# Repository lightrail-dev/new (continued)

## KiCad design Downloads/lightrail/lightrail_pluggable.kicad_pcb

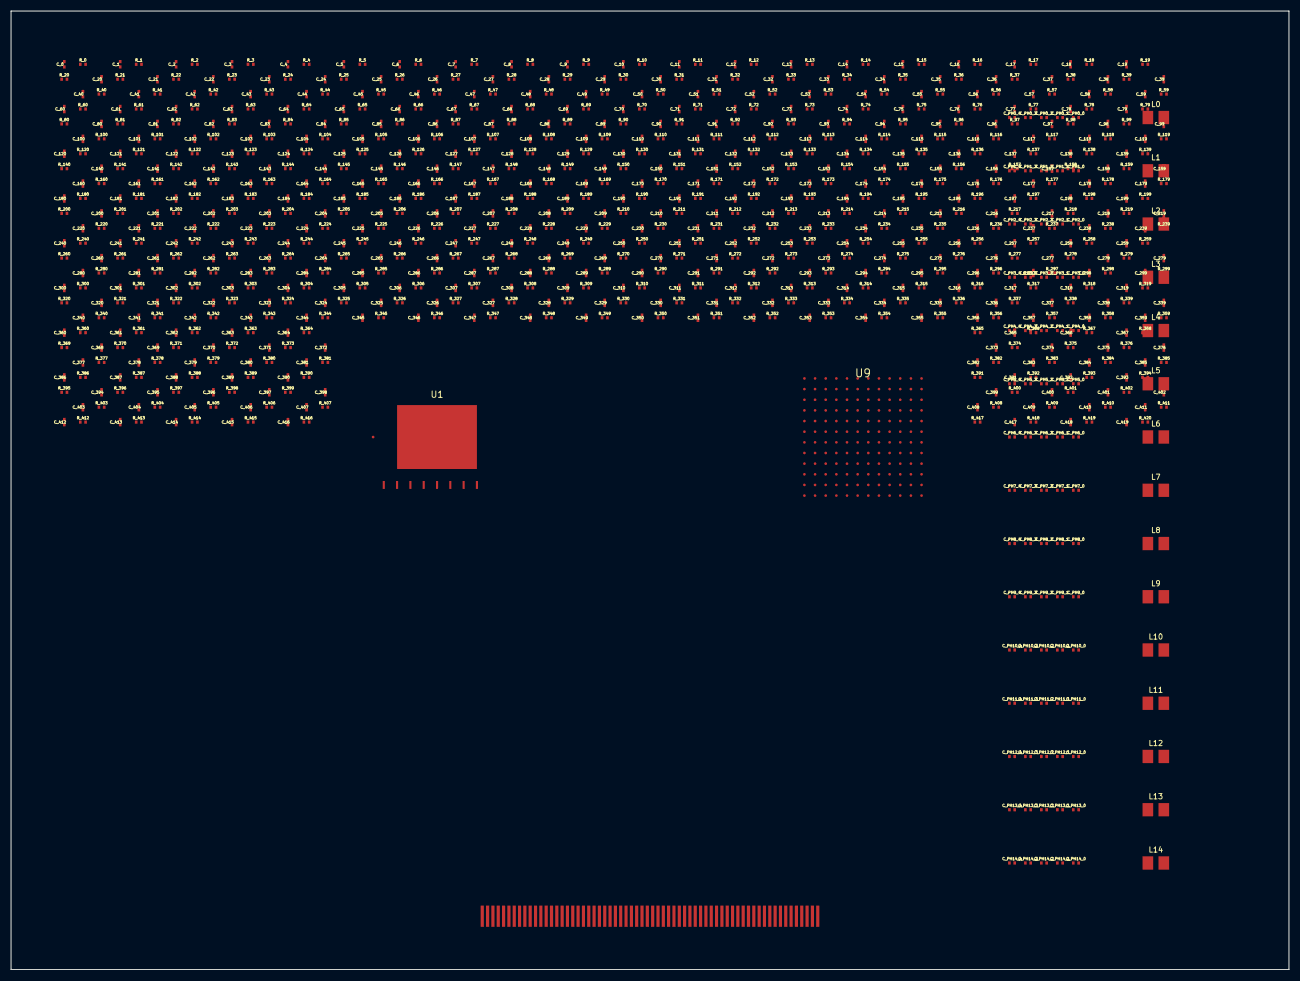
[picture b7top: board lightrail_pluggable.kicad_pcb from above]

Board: 15 copper layers, 240.0 x 180.0 mm, 933 parts (0 on the bottom side), 110 nets, no tracks yet.

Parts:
C_0, C_1, C_2, C_3, C_4, C_5, C_6, C_7, C_8, C_9, C_10, C_11, C_12, C_13, C_14, C_15, C_16, C_17, C_18, C_19, C_20, C_21, C_22, C_23, C_24, C_25, C_26, C_27, C_28, C_29, C_30, C_31, C_32, C_33, C_34, C_35, C_36, C_37, C_38, C_39, C_40, C_41, C_42, C_43, C_44, C_45, C_46, C_47, C_48, C_49, C_50, C_51, C_52, C_53, C_54, C_55, C_56, C_57, C_58, C_59, C_60, C_61, C_62, C_63, C_64, C_65, C_66, C_67, C_68, C_69, C_70, C_71, C_72, C_73, C_74, C_75, C_76, C_77, C_78, C_79, C_80, C_81, C_82, C_83, C_84, C_85, C_86, C_87, C_88, C_89, C_90, C_91, C_92, C_93, C_94, C_95, C_96, C_97, C_98, C_99, C_100, C_101, C_102, C_103, C_104, C_105, C_106, C_107, C_108, C_109, C_110, C_111, C_112, C_113, C_114, C_115, C_116, C_117, C_118, C_119, C_120, C_121, C_122, C_123, C_124, C_125, C_126, C_127, C_128, C_129, C_130, C_131, C_132, C_133, C_134, C_135, C_136, C_137, C_138, C_139, C_140, C_141, C_142, C_143, C_144, C_145, C_146, C_147, C_148, C_149, C_150, C_151, C_152, C_153, C_154, C_155, C_156, C_157, C_158, C_159, C_160, C_161, C_162, C_163, C_164, C_165, C_166, C_167, C_168, C_169, C_170, C_171, C_172, C_173, C_174, C_175, C_176, C_177, C_178, C_179, C_180, C_181, C_182, C_183, C_184, C_185, C_186, C_187, C_188, C_189, C_190, C_191, C_192, C_193, C_194, C_195, C_196, C_197, C_198, C_199, C_200, C_201, C_202, C_203, C_204, C_205, C_206, C_207, C_208, C_209, C_210, C_211, C_212, C_213, C_214, C_215, C_216, C_217, C_218, C_219, C_220, C_221, C_222, C_223, C_224, C_225, C_226, C_227, C_228, C_229, C_230, C_231, C_232, C_233, C_234, C_235, C_236, C_237, C_238, C_239, C_240, C_241, C_242, C_243, C_244, C_245, C_246, C_247, C_248, C_249, C_250, C_251, C_252, C_253, C_254, C_255, C_256, C_257, C_258, C_259, C_260, C_261, C_262, C_263, C_264, C_265, C_266, C_267, C_268, C_269, C_270, C_271, C_272, C_273, C_274, C_275, C_276, C_277, C_278, C_279, C_280, C_281, C_282, C_283, C_284, C_285, C_286, C_287, C_288, C_289, C_290, C_291, C_292, C_293, C_294, C_295, C_296, C_297, C_298, C_299, C_300, C_301, C_302, C_303, C_304, C_305, C_306, C_307, C_308, C_309, C_310, C_311, C_312, C_313, C_314, C_315, C_316, C_317, C_318, C_319, C_320, C_321, C_322, C_323, C_324, C_325, C_326, C_327, C_328, C_329, C_330, C_331, C_332, C_333, C_334, C_335, C_336, C_337, C_338, C_339, C_340, C_341, C_342, C_343, C_344, C_345, C_346, C_347, C_348, C_349, C_350, C_351, C_352, C_353, C_354, C_355, C_356, C_357, C_358, C_359, C_360, C_361, C_362, C_363, C_364, C_365, C_366, C_367, C_368, C_369, C_370, C_371, C_372, C_373, C_374, C_375, C_376, C_377, C_378, C_379, C_380, C_381, C_382, C_383, C_384, C_385, C_386, C_387, C_388, C_389, C_390, C_391, C_392, C_393, C_394, C_395, C_396, C_397, C_398, C_399, C_400, C_401, C_402, C_403, C_404, C_405, C_406, C_407, C_408, C_409, C_410, C_411, C_412, C_413, C_414, C_415, C_416, C_417, C_418, C_419: C_0402
C_PH0_0, C_PH0_1, C_PH0_2, C_PH0_3, C_PH0_4, C_PH1_0, C_PH1_1, C_PH1_2, C_PH1_3, C_PH1_4, C_PH2_0, C_PH2_1, C_PH2_2, C_PH2_3, C_PH2_4, C_PH3_0, C_PH3_1, C_PH3_2, C_PH3_3, C_PH3_4, C_PH4_0, C_PH4_1, C_PH4_2, C_PH4_3, C_PH4_4, C_PH5_0, C_PH5_1, C_PH5_2, C_PH5_3, C_PH5_4, C_PH6_0, C_PH6_1, C_PH6_2, C_PH6_3, C_PH6_4, C_PH7_0, C_PH7_1, C_PH7_2, C_PH7_3, C_PH7_4, C_PH8_0, C_PH8_1, C_PH8_2, C_PH8_3, C_PH8_4, C_PH9_0, C_PH9_1, C_PH9_2, C_PH9_3, C_PH9_4, C_PH10_0, C_PH10_1, C_PH10_2, C_PH10_3, C_PH10_4, C_PH11_0, C_PH11_1, C_PH11_2, C_PH11_3, C_PH11_4, C_PH12_0, C_PH12_1, C_PH12_2, C_PH12_3, C_PH12_4, C_PH13_0, C_PH13_1, C_PH13_2, C_PH13_3, C_PH13_4, C_PH14_0, C_PH14_1, C_PH14_2, C_PH14_3, C_PH14_4: C_0402
L0, L1, L2, L3, L4, L5, L6, L7, L8, L9, L10, L11, L12, L13, L14: L_1210
R_0, R_1, R_2, R_3, R_4, R_5, R_6, R_7, R_8, R_9, R_10, R_11, R_12, R_13, R_14, R_15, R_16, R_17, R_18, R_19, R_20, R_21, R_22, R_23, R_24, R_25, R_26, R_27, R_28, R_29, R_30, R_31, R_32, R_33, R_34, R_35, R_36, R_37, R_38, R_39, R_40, R_41, R_42, R_43, R_44, R_45, R_46, R_47, R_48, R_49, R_50, R_51, R_52, R_53, R_54, R_55, R_56, R_57, R_58, R_59, R_60, R_61, R_62, R_63, R_64, R_65, R_66, R_67, R_68, R_69, R_70, R_71, R_72, R_73, R_74, R_75, R_76, R_77, R_78, R_79, R_80, R_81, R_82, R_83, R_84, R_85, R_86, R_87, R_88, R_89, R_90, R_91, R_92, R_93, R_94, R_95, R_96, R_97, R_98, R_99, R_100, R_101, R_102, R_103, R_104, R_105, R_106, R_107, R_108, R_109, R_110, R_111, R_112, R_113, R_114, R_115, R_116, R_117, R_118, R_119, R_120, R_121, R_122, R_123, R_124, R_125, R_126, R_127, R_128, R_129, R_130, R_131, R_132, R_133, R_134, R_135, R_136, R_137, R_138, R_139, R_140, R_141, R_142, R_143, R_144, R_145, R_146, R_147, R_148, R_149, R_150, R_151, R_152, R_153, R_154, R_155, R_156, R_157, R_158, R_159, R_160, R_161, R_162, R_163, R_164, R_165, R_166, R_167, R_168, R_169, R_170, R_171, R_172, R_173, R_174, R_175, R_176, R_177, R_178, R_179, R_180, R_181, R_182, R_183, R_184, R_185, R_186, R_187, R_188, R_189, R_190, R_191, R_192, R_193, R_194, R_195, R_196, R_197, R_198, R_199, R_200, R_201, R_202, R_203, R_204, R_205, R_206, R_207, R_208, R_209, R_210, R_211, R_212, R_213, R_214, R_215, R_216, R_217, R_218, R_219, R_220, R_221, R_222, R_223, R_224, R_225, R_226, R_227, R_228, R_229, R_230, R_231, R_232, R_233, R_234, R_235, R_236, R_237, R_238, R_239, R_240, R_241, R_242, R_243, R_244, R_245, R_246, R_247, R_248, R_249, R_250, R_251, R_252, R_253, R_254, R_255, R_256, R_257, R_258, R_259, R_260, R_261, R_262, R_263, R_264, R_265, R_266, R_267, R_268, R_269, R_270, R_271, R_272, R_273, R_274, R_275, R_276, R_277, R_278, R_279, R_280, R_281, R_282, R_283, R_284, R_285, R_286, R_287, R_288, R_289, R_290, R_291, R_292, R_293, R_294, R_295, R_296, R_297, R_298, R_299, R_300, R_301, R_302, R_303, R_304, R_305, R_306, R_307, R_308, R_309, R_310, R_311, R_312, R_313, R_314, R_315, R_316, R_317, R_318, R_319, R_320, R_321, R_322, R_323, R_324, R_325, R_326, R_327, R_328, R_329, R_330, R_331, R_332, R_333, R_334, R_335, R_336, R_337, R_338, R_339, R_340, R_341, R_342, R_343, R_344, R_345, R_346, R_347, R_348, R_349, R_350, R_351, R_352, R_353, R_354, R_355, R_356, R_357, R_358, R_359, R_360, R_361, R_362, R_363, R_364, R_365, R_366, R_367, R_368, R_369, R_370, R_371, R_372, R_373, R_374, R_375, R_376, R_377, R_378, R_379, R_380, R_381, R_382, R_383, R_384, R_385, R_386, R_387, R_388, R_389, R_390, R_391, R_392, R_393, R_394, R_395, R_396, R_397, R_398, R_399, R_400, R_401, R_402, R_403, R_404, R_405, R_406, R_407, R_408, R_409, R_410, R_411, R_412, R_413, R_414, R_415, R_416, R_417, R_418, R_419, R_420: R_0402
U1: TFLN_MZM_400G
U9: BCM84881_BGA

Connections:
GND: C_0.2, C_1.2, C_2.2, C_3.2, C_4.2, C_5.2, C_6.2, C_7.2, C_8.2, C_9.2, C_10.2, C_11.2, C_12.2, C_13.2, C_14.2, C_15.2, C_16.2, C_17.2, C_18.2, C_19.2, C_20.2, C_21.2, C_22.2, C_23.2, C_24.2, C_25.2, C_26.2, C_27.2, C_28.2, C_29.2, C_30.2, C_31.2, C_32.2, C_33.2, C_34.2, C_35.2, C_36.2, C_37.2, C_38.2, C_39.2, C_40.2, C_41.2, C_42.2, C_43.2, C_44.2, C_45.2, C_46.2, C_47.2, C_48.2, C_49.2, C_50.2, C_51.2, C_52.2, C_53.2, C_54.2, C_55.2, C_56.2, C_57.2, C_58.2, C_59.2, C_60.2, C_61.2, C_62.2, C_63.2, C_64.2, C_65.2, C_66.2, C_67.2, C_68.2, C_69.2, C_70.2, C_71.2, C_72.2, C_73.2, C_74.2, C_75.2, C_76.2, C_77.2, C_78.2, C_79.2, C_80.2, C_81.2, C_82.2, C_83.2, C_84.2, C_85.2, C_86.2, C_87.2, C_88.2, C_89.2, C_90.2, C_91.2, C_92.2, C_93.2, C_94.2, C_95.2, C_96.2, C_97.2, C_98.2, C_99.2, C_100.2, C_101.2, C_102.2, C_103.2, C_104.2, C_105.2, C_106.2, C_107.2, C_108.2, C_109.2, C_110.2, C_111.2, C_112.2, C_113.2, C_114.2, C_115.2, C_116.2, C_117.2, C_118.2, C_119.2, C_120.2, C_121.2, C_122.2, C_123.2, C_124.2, C_125.2, C_126.2, C_127.2, C_128.2, C_129.2, C_130.2, C_131.2, C_132.2, C_133.2, C_134.2, C_135.2, C_136.2, C_137.2, C_138.2, C_139.2, C_140.2, C_141.2, C_142.2, C_143.2, C_144.2, C_145.2, C_146.2, C_147.2, C_148.2, C_149.2, C_150.2, C_151.2, C_152.2, C_153.2, C_154.2, C_155.2, C_156.2, C_157.2, C_158.2, C_159.2, C_160.2, C_161.2, C_162.2, C_163.2, C_164.2, C_165.2, C_166.2, C_167.2, C_168.2, C_169.2, C_170.2, C_171.2, C_172.2, C_173.2, C_174.2, C_175.2, C_176.2, C_177.2, C_178.2, C_179.2, C_180.2, C_181.2, C_182.2, C_183.2, C_184.2, C_185.2, C_186.2, C_187.2, C_188.2, C_189.2, C_190.2, C_191.2, C_192.2, C_193.2, C_194.2, C_195.2, C_196.2, C_197.2, C_198.2, C_199.2, C_200.2, C_201.2, C_202.2, C_203.2, C_204.2, C_205.2, C_206.2, C_207.2, C_208.2, C_209.2, C_210.2, C_211.2, C_212.2, C_213.2, C_214.2, C_215.2, C_216.2, C_217.2, C_218.2, C_219.2, C_220.2, C_221.2, C_222.2, C_223.2, C_224.2, C_225.2, C_226.2, C_227.2, C_228.2, C_229.2, C_230.2, C_231.2, C_232.2, C_233.2, C_234.2, C_235.2, C_236.2, C_237.2, C_238.2, C_239.2, C_240.2, C_241.2, C_242.2, C_243.2, C_244.2, C_245.2, C_246.2, C_247.2, C_248.2, C_249.2, C_250.2, C_251.2, C_252.2, C_253.2, C_254.2, C_255.2, C_256.2, C_257.2, C_258.2, C_259.2, C_260.2, C_261.2, C_262.2, C_263.2, C_264.2, C_265.2, C_266.2, C_267.2, C_268.2, C_269.2, C_270.2, C_271.2, C_272.2, C_273.2, C_274.2, C_275.2, C_276.2, C_277.2, C_278.2, C_279.2, C_280.2, C_281.2, C_282.2, C_283.2, C_284.2, C_285.2, C_286.2, C_287.2, C_288.2, C_289.2, C_290.2, C_291.2, C_292.2, C_293.2, C_294.2, C_295.2, C_296.2, C_297.2, C_298.2, C_299.2, C_300.2, C_301.2, C_302.2, C_303.2, C_304.2, C_305.2, C_306.2, C_307.2, C_308.2, C_309.2, C_310.2, C_311.2, C_312.2, C_313.2, C_314.2, C_315.2, C_316.2, C_317.2, C_318.2, C_319.2, C_320.2, C_321.2, C_322.2, C_323.2, C_324.2, C_325.2, C_326.2, C_327.2, C_328.2, C_329.2, C_330.2, C_331.2, C_332.2, C_333.2, C_334.2, C_335.2, C_336.2, C_337.2, C_338.2, C_339.2, C_340.2, C_341.2, C_342.2, C_343.2, C_344.2, C_345.2, C_346.2, C_347.2, C_348.2, C_349.2, C_350.2, C_351.2, C_352.2, C_353.2, C_354.2, C_355.2, C_356.2, C_357.2, C_358.2, C_359.2, C_360.2, C_361.2, C_362.2, C_363.2, C_364.2, C_365.2, C_366.2, C_367.2, C_368.2, C_369.2, C_370.2, C_371.2, C_372.2, C_373.2, C_374.2, C_375.2, C_376.2, C_377.2, C_378.2, C_379.2, C_380.2, C_381.2, C_382.2, C_383.2, C_384.2, C_385.2, C_386.2, C_387.2, C_388.2, C_389.2, C_390.2, C_391.2, C_392.2, C_393.2, C_394.2, C_395.2, C_396.2, C_397.2, C_398.2, C_399.2, C_400.2, C_401.2, C_402.2, C_403.2, C_404.2, C_405.2, C_406.2, C_407.2, C_408.2, C_409.2, C_410.2, C_411.2, C_412.2, C_413.2, C_414.2, C_415.2, C_416.2, C_417.2, C_418.2, C_419.2, C_PH0_0.2, C_PH0_1.2, C_PH0_2.2, C_PH0_3.2, C_PH0_4.2, C_PH1_0.2, C_PH1_1.2, C_PH1_2.2, C_PH1_3.2, C_PH1_4.2, C_PH2_0.2, C_PH2_1.2, C_PH2_2.2, C_PH2_3.2, C_PH2_4.2, C_PH3_0.2, C_PH3_1.2, C_PH3_2.2, C_PH3_3.2, C_PH3_4.2, C_PH4_0.2, C_PH4_1.2, C_PH4_2.2, C_PH4_3.2, C_PH4_4.2, C_PH5_0.2, C_PH5_1.2, C_PH5_2.2, C_PH5_3.2, C_PH5_4.2, C_PH6_0.2, C_PH6_1.2, C_PH6_2.2, C_PH6_3.2, C_PH6_4.2, C_PH7_0.2, C_PH7_1.2, C_PH7_2.2, C_PH7_3.2, C_PH7_4.2, C_PH8_0.2, C_PH8_1.2, C_PH8_2.2, C_PH8_3.2, C_PH8_4.2, C_PH9_0.2, C_PH9_1.2, C_PH9_2.2, C_PH9_3.2, C_PH9_4.2, C_PH10_0.2, C_PH10_1.2, C_PH10_2.2, C_PH10_3.2, C_PH10_4.2, C_PH11_0.2, C_PH11_1.2, C_PH11_2.2, C_PH11_3.2, C_PH11_4.2, C_PH12_0.2, C_PH12_1.2, C_PH12_2.2, C_PH12_3.2, C_PH12_4.2, C_PH13_0.2, C_PH13_1.2, C_PH13_2.2, C_PH13_3.2, C_PH13_4.2, C_PH14_0.2, C_PH14_1.2, C_PH14_2.2, C_PH14_3.2, C_PH14_4.2, R_0.2, R_1.2, R_2.2, R_3.2, R_4.2, R_5.2, R_6.2, R_7.2, R_8.2, R_9.2, R_10.2, R_11.2, R_12.2, R_13.2, R_14.2, R_15.2, R_16.2, R_17.2, R_18.2, R_19.2, R_20.2, R_21.2, R_22.2, R_23.2, R_24.2, R_25.2, R_26.2, R_27.2, R_28.2, R_29.2, R_30.2, R_31.2, R_32.2, R_33.2, R_34.2, R_35.2, R_36.2, R_37.2, R_38.2, R_39.2, R_40.2, R_41.2, R_42.2, R_43.2, R_44.2, R_45.2, R_46.2, R_47.2, R_48.2, R_49.2, R_50.2, R_51.2, R_52.2, R_53.2, R_54.2, R_55.2, R_56.2, R_57.2, R_58.2, R_59.2, R_60.2, R_61.2, R_62.2, R_63.2, R_64.2, R_65.2, R_66.2, R_67.2, R_68.2, R_69.2, R_70.2, R_71.2, R_72.2, R_73.2, R_74.2, R_75.2, R_76.2, R_77.2, R_78.2, R_79.2, R_80.2, R_81.2, R_82.2, R_83.2, R_84.2, R_85.2, R_86.2, R_87.2, R_88.2, R_89.2, R_90.2, R_91.2, R_92.2, R_93.2, R_94.2, R_95.2, R_96.2, R_97.2, R_98.2, R_99.2, R_100.2, R_101.2, R_102.2, R_103.2, R_104.2, R_105.2, R_106.2, R_107.2, R_108.2, R_109.2, R_110.2, R_111.2, R_112.2, R_113.2, R_114.2, R_115.2, R_116.2, R_117.2, R_118.2, R_119.2, R_120.2, R_121.2, R_122.2, R_123.2, R_124.2, R_125.2, R_126.2, R_127.2, R_128.2, R_129.2, R_130.2, R_131.2, R_132.2, R_133.2, R_134.2, R_135.2, R_136.2, R_137.2, R_138.2, R_139.2, R_140.2, R_141.2, R_142.2, R_143.2, R_144.2, R_145.2, R_146.2, R_147.2, R_148.2, R_149.2, R_150.2, R_151.2, R_152.2, R_153.2, R_154.2, R_155.2, R_156.2, R_157.2, R_158.2, R_159.2, R_160.2, R_161.2, R_162.2, R_163.2, R_164.2, R_165.2, R_166.2, R_167.2, R_168.2, R_169.2, R_170.2, R_171.2, R_172.2, R_173.2, R_174.2, R_175.2, R_176.2, R_177.2, R_178.2, R_179.2, R_180.2, R_181.2, R_182.2, R_183.2, R_184.2, R_185.2, R_186.2, R_187.2, R_188.2, R_189.2, R_190.2, R_191.2, R_192.2, R_193.2, R_194.2, R_195.2, R_196.2, R_197.2, R_198.2, R_199.2, R_200.2, R_201.2, R_202.2, R_203.2, R_204.2, R_205.2, R_206.2, R_207.2, R_208.2, R_209.2, R_210.2, R_211.2, R_212.2, R_213.2, R_214.2, R_215.2, R_216.2, R_217.2, R_218.2, R_219.2, R_220.2, R_221.2, R_222.2, R_223.2, R_224.2, R_225.2, R_226.2, R_227.2, R_228.2, R_229.2, R_230.2, R_231.2, R_232.2, R_233.2, R_234.2, R_235.2, R_236.2, R_237.2, R_238.2, R_239.2, R_240.2, R_241.2, R_242.2, R_243.2, R_244.2, R_245.2, R_246.2, R_247.2, R_248.2, R_249.2, R_250.2, R_251.2, R_252.2, R_253.2, R_254.2, R_255.2, R_256.2, R_257.2, R_258.2, R_259.2, R_260.2, R_261.2, R_262.2, R_263.2, R_264.2, R_265.2, R_266.2, R_267.2, R_268.2, R_269.2, R_270.2, R_271.2, R_272.2, R_273.2, R_274.2, R_275.2, R_276.2, R_277.2, R_278.2, R_279.2, R_280.2, R_281.2, R_282.2, R_283.2, R_284.2, R_285.2, R_286.2, R_287.2, R_288.2, R_289.2, R_290.2, R_291.2, R_292.2, R_293.2, R_294.2, R_295.2, R_296.2, R_297.2, R_298.2, R_299.2, R_300.2, R_301.2, R_302.2, R_303.2, R_304.2, R_305.2, R_306.2, R_307.2, R_308.2, R_309.2, R_310.2, R_311.2, R_312.2, R_313.2, R_314.2, R_315.2, R_316.2, R_317.2, R_318.2, R_319.2, R_320.2, R_321.2, R_322.2, R_323.2, R_324.2, R_325.2, R_326.2, R_327.2, R_328.2, R_329.2, R_330.2, R_331.2, R_332.2, R_333.2, R_334.2, R_335.2, R_336.2, R_337.2, R_338.2, R_339.2, R_340.2, R_341.2, R_342.2, R_343.2, R_344.2, R_345.2, R_346.2, R_347.2, R_348.2, R_349.2, R_350.2, R_351.2, R_352.2, R_353.2, R_354.2, R_355.2, R_356.2, R_357.2, R_358.2, R_359.2, R_360.2, R_361.2, R_362.2, R_363.2, R_364.2, R_365.2, R_366.2, R_367.2, R_368.2, R_369.2, R_370.2, R_371.2, R_372.2, R_373.2, R_374.2, R_375.2, R_376.2, R_377.2, R_378.2, R_379.2, R_380.2, R_381.2, R_382.2, R_383.2, R_384.2, R_385.2, R_386.2, R_387.2, R_388.2, R_389.2, R_390.2, R_391.2, R_392.2, R_393.2, R_394.2, R_395.2, R_396.2, R_397.2, R_398.2, R_399.2, R_400.2, R_401.2, R_402.2, R_403.2, R_404.2, R_405.2, R_406.2, R_407.2, R_408.2, R_409.2, R_410.2, R_411.2, R_412.2, R_413.2, R_414.2, R_415.2, R_416.2, R_417.2, R_418.2, R_419.2, R_420.2, U1.TH
SIG_0: R_34.1, R_60.1, R_75.1, R_123.1, R_291.1, R_345.1, U9.8_4
SIG_1: R_28.1, R_126.1, R_140.1, R_387.1, U9.8_5
SIG_2: R_93.1, R_114.1, R_294.1, U9.8_6
SIG_3: R_76.1, R_82.1, R_175.1, R_228.1, U9.8_7
SIG_4: R_68.1, R_196.1, R_200.1, R_213.1, R_250.1, R_251.1, R_290.1, R_358.1, U9.8_8
SIG_5: R_109.1, R_416.1, R_419.1, U9.8_9
SIG_6: R_212.1, R_261.1, R_335.1, R_351.1, R_384.1, R_394.1, U9.8_10
SIG_7: R_31.1, R_49.1, R_73.1, R_80.1, R_113.1, U9.8_11
SIG_8: R_88.1, R_115.1, R_264.1, U9.9_0
SIG_9: R_129.1, R_282.1, R_288.1, R_317.1, U9.9_1
SIG_10: R_147.1, U9.9_2
SIG_11: R_409.1, U9.9_3
SIG_12: R_230.1, R_391.1, U9.9_4
SIG_13: R_156.1, R_202.1, R_389.1, R_404.1, U9.9_5
SIG_14: R_186.1, R_243.1, R_255.1, R_273.1, R_352.1, R_365.1, R_397.1, R_405.1, R_410.1, U9.9_6
SIG_15: R_1.1, R_25.1, R_53.1, R_74.1, R_112.1, R_143.1, R_180.1, R_309.1, R_399.1, U9.9_7
SIG_16: R_204.1, R_217.1, R_237.1, U9.9_8
SIG_17: R_218.1, R_234.1, R_266.1, R_321.1, R_401.1, U9.9_9
SIG_18: R_222.1, R_271.1, R_372.1, U9.9_10
SIG_19: R_18.1, R_55.1, R_135.1, R_305.1, R_320.1, U9.9_11
SIG_20: R_4.1, R_209.1, R_377.1
SIG_21: R_70.1, R_102.1, R_105.1, R_388.1
SIG_22: R_54.1, R_145.1, R_238.1
SIG_23: R_280.1, R_316.1
SIG_24: R_151.1, R_165.1, R_314.1
SIG_25: R_50.1, R_239.1, R_382.1
SIG_26: R_127.1, R_268.1, R_333.1
SIG_28: R_32.1, R_97.1, R_111.1, R_272.1, R_298.1
SIG_29: R_43.1, R_285.1, R_292.1, R_362.1
SIG_30: R_155.1, R_195.1, R_295.1, R_318.1
SIG_31: R_5.1, R_36.1, R_71.1, R_92.1, R_100.1, R_176.1
SIG_32: R_30.1, R_94.1, R_177.1, R_184.1, R_247.1, R_402.1
SIG_33: R_72.1, R_132.1, R_210.1, R_211.1, R_219.1, R_332.1, R_383.1
SIG_34: R_37.1, R_240.1, R_408.1
SIG_35: R_8.1, R_95.1, R_133.1, R_201.1, R_215.1, R_311.1, R_337.1, R_417.1
SIG_36: R_101.1, R_252.1
SIG_37: R_14.1, R_33.1, R_106.1, R_139.1, R_157.1, R_198.1
SIG_38: R_17.1, R_19.1, R_191.1
SIG_39: R_56.1, R_141.1, R_203.1, R_281.1, R_334.1, R_361.1, R_374.1
SIG_40: R_182.1, R_223.1, R_265.1, R_339.1
SIG_41: R_77.1, R_121.1, R_286.1, R_302.1, R_330.1
SIG_42: R_3.1, R_179.1
SIG_43: R_183.1, R_188.1, R_279.1
SIG_44: R_44.1, R_168.1, R_233.1, R_267.1, R_308.1, R_323.1, R_392.1
SIG_45: R_22.1, R_66.1, R_246.1, R_395.1
SIG_46: R_21.1, R_24.1, R_244.1, R_400.1
SIG_47: R_124.1, R_312.1, R_327.1, R_328.1, R_371.1, R_393.1
SIG_48: R_46.1, R_144.1, R_306.1, R_390.1
SIG_49: R_216.1, R_307.1
SIG_50: R_83.1, R_134.1, R_283.1, R_353.1
SIG_51: R_13.1, R_38.1
SIG_52: R_45.1, R_69.1, R_245.1, R_296.1, R_396.1
SIG_53: R_40.1, R_122.1, R_221.1, R_235.1, R_357.1
SIG_54: R_57.1, R_259.1, R_338.1
SIG_55: R_300.1, R_364.1, R_407.1
SIG_56: R_163.1, R_205.1, R_299.1, R_301.1, R_403.1
SIG_57: R_9.1, R_39.1, R_185.1, R_236.1, R_278.1, R_329.1, R_342.1, R_420.1
SIG_58: R_6.1, R_90.1, R_149.1, R_263.1, R_269.1
SIG_59: R_12.1, R_153.1, R_277.1, R_418.1
SIG_60: R_174.1, R_224.1, R_241.1, R_348.1
SIG_61: R_199.1, R_347.1, R_350.1
SIG_62: R_326.1, R_336.1, R_343.1, R_411.1
SIG_63: R_20.1, R_42.1, R_96.1, R_232.1, R_324.1
SIG_64: R_171.1, R_406.1
SIG_65: R_89.1, R_136.1, R_225.1, R_231.1, R_363.1
SIG_66: R_48.1, R_242.1, R_284.1, R_297.1, R_331.1, R_360.1, R_366.1
SIG_67: R_81.1, R_117.1, R_303.1
SIG_68: R_67.1, R_150.1, R_274.1
SIG_70: R_118.1, R_172.1, R_226.1, R_344.1, R_369.1, R_414.1
SIG_72: R_78.1, R_207.1, R_319.1, R_325.1, U9.6_0
SIG_73: R_2.1, R_128.1, R_356.1, U9.6_1
SIG_74: R_178.1, R_256.1, R_304.1, U9.6_2
SIG_75: R_52.1, R_158.1, R_315.1, R_370.1, U9.6_3
SIG_76: R_7.1, R_15.1, R_192.1, R_193.1, R_378.1, U9.6_4
SIG_77: R_11.1, R_26.1, R_86.1, R_99.1, R_368.1, R_386.1, U9.6_5
SIG_78: R_130.1, R_142.1, R_376.1, U9.6_6
SIG_79: R_65.1, R_148.1, R_253.1, R_293.1, R_359.1, U9.6_7
SIG_80: R_59.1, R_120.1, R_160.1, R_164.1, R_214.1, R_367.1, R_413.1, U9.6_8
SIG_81: R_27.1, R_61.1, R_138.1, R_220.1, R_229.1, R_257.1, U9.6_9
SIG_82: R_41.1, R_119.1, R_249.1, R_289.1, R_379.1, U9.6_10
SIG_83: R_248.1, R_260.1, U9.6_11
SIG_84: R_47.1, R_355.1, U9.7_0
SIG_85: R_51.1, R_87.1, R_137.1, R_194.1, R_270.1, U9.7_1
SIG_86: R_167.1, R_310.1, R_373.1, U9.7_2
SIG_87: R_146.1, R_162.1, R_166.1, R_197.1, R_206.1, R_275.1, R_349.1, U9.7_3
SIG_88: R_63.1, R_181.1, R_254.1, U9.7_4
SIG_89: R_116.1, R_152.1, R_161.1, R_169.1, R_258.1, R_276.1, R_287.1, U9.7_5
SIG_90: R_10.1, R_98.1, R_131.1, R_322.1, R_354.1, U9.7_6
SIG_91: R_23.1, R_103.1, R_170.1, R_227.1, U9.7_7
SIG_92: R_62.1, R_187.1, R_346.1, R_385.1, U9.7_8
SIG_93: R_35.1, R_79.1, R_398.1, R_412.1, U9.7_9
SIG_94: R_84.1, R_125.1, R_173.1, R_189.1, R_262.1, R_341.1, U9.7_10
SIG_95: R_0.1, R_104.1, R_108.1, R_110.1, R_208.1, U9.7_11
SIG_96: R_58.1, R_91.1, R_380.1, R_381.1, U9.8_0
SIG_97: R_29.1, U9.8_1
SIG_98: R_64.1, R_190.1, R_340.1, U9.8_2
SIG_99: R_16.1, R_85.1, R_154.1, R_313.1, R_415.1, U9.8_3
TFLN_RF_CH0: U1.0, U9.5_4
TFLN_RF_CH1: U1.1, U9.5_5
TFLN_RF_CH2: U1.2, U9.5_6
TFLN_RF_CH3: U1.3, U9.5_7
TFLN_RF_CH4: U1.4, U9.5_8
TFLN_RF_CH5: U1.5, U9.5_9
TFLN_RF_CH6: U1.6, U9.5_10
TFLN_RF_CH7: U1.7, U9.5_11
VCC_1V8: C_6.1, C_7.1, C_12.1, C_13.1, C_16.1, C_18.1, C_19.1, C_21.1, C_23.1, C_26.1, C_30.1, C_34.1, C_35.1, C_40.1, C_43.1, C_44.1, C_46.1, C_50.1, C_52.1, C_53.1, C_54.1, C_55.1, C_56.1, C_57.1, C_59.1, C_62.1, C_66.1, C_78.1, C_82.1, C_86.1, C_88.1, C_95.1, C_104.1, C_109.1, C_110.1, C_115.1, C_116.1, C_120.1, C_125.1, C_130.1, C_131.1, C_133.1, C_135.1, C_137.1, C_143.1, C_147.1, C_151.1, C_152.1, C_156.1, C_158.1, C_161.1, C_165.1, C_166.1, C_171.1, C_172.1, C_176.1, C_184.1, C_187.1, C_188.1, C_193.1, C_197.1, C_198.1, C_203.1, C_210.1, C_211.1, C_220.1, C_224.1, C_225.1, C_226.1, C_229.1, C_232.1, C_234.1, C_238.1, C_239.1, C_245.1, C_252.1, C_253.1, C_256.1, C_258.1, C_262.1, C_266.1, C_278.1, C_280.1, C_283.1, C_292.1, C_295.1, C_297.1, C_299.1, C_301.1, C_302.1, C_305.1, C_306.1, C_310.1, C_314.1, C_318.1, C_320.1, C_321.1, C_326.1, C_335.1, C_337.1, C_338.1, C_340.1, C_344.1, C_348.1, C_352.1, C_356.1, C_357.1, C_359.1, C_361.1, C_363.1, C_370.1, C_383.1, C_387.1, C_388.1, C_389.1, C_391.1, C_395.1, C_396.1, C_398.1, C_400.1, C_405.1, C_406.1, C_407.1, C_408.1, C_409.1, C_410.1, C_411.1, C_412.1, C_414.1, C_415.1, C_417.1, C_419.1, C_PH0_0.1, C_PH0_1.1, C_PH0_2.1, C_PH0_3.1, C_PH0_4.1, C_PH1_0.1, C_PH1_1.1, C_PH1_2.1, C_PH1_3.1, C_PH1_4.1, C_PH2_0.1, C_PH2_1.1, C_PH2_2.1, C_PH2_3.1, C_PH2_4.1, C_PH3_0.1, C_PH3_1.1, C_PH3_2.1, C_PH3_3.1, C_PH3_4.1, C_PH4_0.1, C_PH4_1.1, C_PH4_2.1, C_PH4_3.1, C_PH4_4.1, C_PH5_0.1, C_PH5_1.1, C_PH5_2.1, C_PH5_3.1, C_PH5_4.1, C_PH6_0.1, C_PH6_1.1, C_PH6_2.1, C_PH6_3.1, C_PH6_4.1, C_PH7_0.1, C_PH7_1.1, C_PH7_2.1, C_PH7_3.1, C_PH7_4.1, C_PH8_0.1, C_PH8_1.1, C_PH8_2.1, C_PH8_3.1, C_PH8_4.1, C_PH9_0.1, C_PH9_1.1, C_PH9_2.1, C_PH9_3.1, C_PH9_4.1, C_PH10_0.1, C_PH10_1.1, C_PH10_2.1, C_PH10_3.1, C_PH10_4.1, C_PH11_0.1, C_PH11_1.1, C_PH11_2.1, C_PH11_3.1, C_PH11_4.1, C_PH12_0.1, C_PH12_1.1, C_PH12_2.1, C_PH12_3.1, C_PH12_4.1, C_PH13_0.1, C_PH13_1.1, C_PH13_2.1, C_PH13_3.1, C_PH13_4.1, C_PH14_0.1, C_PH14_1.1, C_PH14_2.1, C_PH14_3.1, C_PH14_4.1, L0.2, L1.2, L2.2, L3.2, L4.2, L5.2, L6.2, L7.2, L8.2, L9.2, L10.2, L11.2, L12.2, L13.2, L14.2, U9.10_0, U9.10_1, U9.10_2, U9.10_3, U9.10_4, U9.10_5, U9.10_6, U9.10_7, U9.10_8, U9.10_9, U9.10_10, U9.10_11, U9.11_0, U9.11_1, U9.11_2, U9.11_3, U9.11_4, U9.11_5, U9.11_6, U9.11_7, U9.11_8, U9.11_9, U9.11_10, U9.11_11
VCC_3V3: C_1.1, C_8.1, C_14.1, C_15.1, C_20.1, C_27.1, C_32.1, C_37.1, C_38.1, C_41.1, C_45.1, C_47.1, C_51.1, C_67.1, C_69.1, C_70.1, C_72.1, C_73.1, C_79.1, C_84.1, C_85.1, C_87.1, C_90.1, C_91.1, C_94.1, C_99.1, C_102.1, C_103.1, C_107.1, C_108.1, C_114.1, C_117.1, C_124.1, C_127.1, C_128.1, C_132.1, C_134.1, C_136.1, C_138.1, C_141.1, C_142.1, C_146.1, C_149.1, C_150.1, C_153.1, C_154.1, C_155.1, C_157.1, C_159.1, C_164.1, C_167.1, C_170.1, C_173.1, C_177.1, C_178.1, C_183.1, C_185.1, C_190.1, C_191.1, C_194.1, C_200.1, C_204.1, C_205.1, C_206.1, C_207.1, C_208.1, C_209.1, C_212.1, C_213.1, C_214.1, C_215.1, C_216.1, C_217.1, C_218.1, C_222.1, C_227.1, C_228.1, C_230.1, C_233.1, C_236.1, C_237.1, C_240.1, C_246.1, C_250.1, C_254.1, C_255.1, C_259.1, C_261.1, C_263.1, C_264.1, C_267.1, C_268.1, C_269.1, C_272.1, C_273.1, C_274.1, C_276.1, C_279.1, C_285.1, C_287.1, C_288.1, C_291.1, C_293.1, C_296.1, C_303.1, C_304.1, C_309.1, C_311.1, C_313.1, C_316.1, C_319.1, C_322.1, C_324.1, C_325.1, C_330.1, C_332.1, C_343.1, C_346.1, C_347.1, C_350.1, C_355.1, C_362.1, C_364.1, C_365.1, C_366.1, C_367.1, C_368.1, C_369.1, C_372.1, C_373.1, C_374.1, C_378.1, C_381.1, C_384.1, C_386.1, C_390.1, C_397.1, C_416.1, C_418.1
VCC_12V: L0.1, L1.1, L2.1, L3.1, L4.1, L5.1, L6.1, L7.1, L8.1, L9.1, L10.1, L11.1, L12.1, L13.1, L14.1
V_BIAS: C_0.1, C_2.1, C_3.1, C_4.1, C_5.1, C_9.1, C_10.1, C_11.1, C_17.1, C_22.1, C_24.1, C_25.1, C_28.1, C_29.1, C_31.1, C_33.1, C_36.1, C_39.1, C_42.1, C_48.1, C_49.1, C_58.1, C_60.1, C_61.1, C_63.1, C_64.1, C_65.1, C_68.1, C_71.1, C_74.1, C_75.1, C_76.1, C_77.1, C_80.1, C_81.1, C_83.1, C_89.1, C_92.1, C_93.1, C_96.1, C_97.1, C_98.1, C_100.1, C_101.1, C_105.1, C_106.1, C_111.1, C_112.1, C_113.1, C_118.1, C_119.1, C_121.1, C_122.1, C_123.1, C_126.1, C_129.1, C_139.1, C_140.1, C_144.1, C_145.1, C_148.1, C_160.1, C_162.1, C_163.1, C_168.1, C_169.1, C_174.1, C_175.1, C_179.1, C_180.1, C_181.1, C_182.1, C_186.1, C_189.1, C_192.1, C_195.1, C_196.1, C_199.1, C_201.1, C_202.1, C_219.1, C_221.1, C_223.1, C_231.1, C_235.1, C_241.1, C_242.1, C_243.1, C_244.1, C_247.1, C_248.1, C_249.1, C_251.1, C_257.1, C_260.1, C_265.1, C_270.1, C_271.1, C_275.1, C_277.1, C_281.1, C_282.1, C_284.1, C_286.1, C_289.1, C_290.1, C_294.1, C_298.1, C_300.1, C_307.1, C_308.1, C_312.1, C_315.1, C_317.1, C_323.1, C_327.1, C_328.1, C_329.1, C_331.1, C_333.1, C_334.1, C_336.1, C_339.1, C_341.1, C_342.1, C_345.1, C_349.1, C_351.1, C_353.1, C_354.1, C_358.1, C_360.1, C_371.1, C_375.1, C_376.1, C_377.1, C_379.1, C_380.1, C_382.1, C_385.1, C_392.1, C_393.1, C_394.1, C_399.1, C_401.1, C_402.1, C_403.1, C_404.1, C_413.1

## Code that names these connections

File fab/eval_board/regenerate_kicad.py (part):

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\t\t(pin "+1V0" input (at 88.9 85.09 180) (effects (font (size 1.27 1.27))) (uuid "{uid()}"))
\t\t(pin "+1V8" input (at 88.9 87.63 180) (effects (font (size 1.27 1.27))) (uuid "{uid()}"))
\t\t(pin "+3V3" input (at 88.9 90.17 180) (effects (font (size 1.27 1.27))) (uuid "{uid()}"))
\t\t(pin "AXI_ACLK" bidirectional (at 133.35 82.55 0) (effects (font (size 1.27 1.27))) (uuid "{uid()}"))
\t\t(pin "JTAG_TDO" output (at 133.35 85.09 0) (effects (font (size 1.27 1.27))) (uuid "{uid()}"))
\t\t(pin "TFLN_TX_P" output (at 133.35 87.63 0) (effects (font (size 1.27 1.27))) (uuid "{uid()}"))
\t\t(pin "HBM_DQ" bidirectional (at 133.35 90.17 0) (effects (font (size 1.27 1.27))) (uuid "{uid()}"))
\t)""")
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\t\t(property "Sheetname" "TFLN_Optical" (at 152.4 74.93 0) (effects (font (size 1.27 1.27))))
\t\t(property "Sheetfile" "sheets/tfln_optical.kicad_sch" (at 152.4 104.14 0) (effects (font (size 1.27 1.27)) (hide yes)))
\t\t(pin "TFLN_TX_P" input (at 152.4 82.55 180) (effects (font (size 1.27 1.27))) (uuid "{uid()}"))
\t\t(pin "SPI_CLK" input (at 152.4 87.63 180) (effects (font (size 1.27 1.27))) (uuid "{uid()}"))
\t\t(pin "I2C_SCL" bidirectional (at 190.5 82.55 0) (effects (font (size 1.27 1.27))) (uuid "{uid()}"))
\t\t(pin "I2C_SDA" bidirectional (at 190.5 85.09 0) (effects (font (size 1.27 1.27))) (uuid "{uid()}"))
\t\t(pin "MPO_FIBER" output (at 190.5 90.17 0) (effects (font (size 1.27 1.27))) (uuid "{uid()}"))
\t)""")

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\t\t(uuid "{sheet_uuids['Clock_Interface']}")
\t\t(property "Sheetname" "Clock_Interface" (at 210.82 74.93 0) (effects (font (size 1.27 1.27))))
\t\t(property "Sheetfile" "sheets/clock_interface.kicad_sch" (at 210.82 104.14 0) (effects (font (size 1.27 1.27)) (hide yes)))
\t\t(pin "CLK_100M" output (at 248.92 82.55 0) (effects (font (size 1.27 1.27))) (uuid "{uid()}"))
\t\t(pin "CLK_HBM" output (at 248.92 85.09 0) (effects (font (size 1.27 1.27))) (uuid "{uid()}"))
\t\t(pin "CLK_SERDES" output (at 248.92 87.63 0) (effects (font (size 1.27 1.27))) (uuid "{uid()}"))
\t\t(pin "USB_DP" bidirectional (at 210.82 82.55 180) (effects (font (size 1.27 1.27))) (uuid "{uid()}"))
\t\t(pin "USB_DN" bidirectional (at 210.82 85.09 180) (effects (font (size 1.27 1.27))) (uuid "{uid()}"))
\t\t(pin "JTAG_TCK" input (at 210.82 90.17 180) (effects (font (size 1.27 1.27))) (uuid "{uid()}"))
\t\t(pin "RESET_N" output (at 248.92 92.71 0) (effects (font (size 1.27 1.27))) (uuid "{uid()}"))
\t)""")

    text = text_note(
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
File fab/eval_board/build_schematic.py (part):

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        "21": "JTAG_TCK", "22": "JTAG_TMS", "23": "JTAG_TDI", "24": "JTAG_TDO",
        "25": "CLK_CORE", "26": "CLK_REF",
        "27": "UART_TX", "28": "UART_RX",
        "29": "FPGA_GPIO0", "30": "FPGA_GPIO1", "31": "FPGA_GPIO2", "32": "FPGA_GPIO3",
    }
    inst, conn = place_instance("FPGA_Xilinx:XC7A100T", "U2", "XC7A100T", 220, 80,
                                 u2_geom, u2_nets, "Package_BGA:BGA-256_14x14mm_P0.8mm", "XC7A100T-1FTG256C")
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    
    # -- J6 GPIO Header 2x7
    gpio_pins = ["+3V3", "GND", "GPIO0", "GPIO1", "GPIO2", "GPIO3",
                 "GPIO4", "GPIO5", "GPIO6", "GPIO7", "GPIO8", "GPIO9", "I2C_SCL", "I2C_SDA"]
    j6_lib, j6_geom = make_lib_sym_connector("Connector:PinHeader_2x07", "J", gpio_pins, "GPIO Expansion")
    lib_syms.append(j6_lib)
    j6_nets = {"1": "+3V3", "2": "GND", "3": "FPGA_GPIO0", "4": "FPGA_GPIO1",
               "5": "FPGA_GPIO2", "6": "FPGA_GPIO3", "13": "I2C_SCL", "14": "I2C_SDA"}
    inst, conn = place_instance("Connector:PinHeader_2x07", "J6", "GPIO", 315, 120,
                                 j6_geom, j6_nets, "Connector_PinHeader_1.27mm:PinHeader_2x07_P1.27mm_Vertical")
    instances.append(inst); connections.append(conn)
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    lib_syms.append(make_lib_sym_pwr_flag())
    hlabels = [place_pwr_flag("+5V_USB", 300, 30)]
    
    text = text_note("Clock Generation + Interface Block\\nSi5395A: 100MHz TCXO → CLK_CORE/REF/SERDES/HBM\\nFT232H: USB-C → UART\\nGPIO header + Reset circuit", 30, 160, 1.5)
    
    return _wrap_subsheet("Clock + Interface - LightRail Eval Board",
                          "f0000004-0004-4000-8000-000000000004",
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
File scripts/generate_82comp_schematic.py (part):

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        w.label_at_pin(NCE, "HBM_CATTRIP", sx, sy, f"{pfx}_CATTRIP")
        w.label_at_pin(NCE, "HBM_PWR_GOOD", sx, sy, f"{pfx}_PWR_GOOD")
        # I2C
        w.label_at_pin(NCE, "I2C_SDA", sx, sy, "I2C_SDA", is_global=True)
        w.label_at_pin(NCE, "I2C_SCL", sx, sy, "I2C_SCL", is_global=True, shape="input")
        # SPI (BMC is master, NCE is slave) – only NCE0 connects to BMC SPI
        if pfx == "NCE0":
            w.label_at_pin(NCE, "SPI_MOSI", sx, sy, "SPI_MOSI", is_global=True, shape="input")
            w.label_at_pin(NCE, "SPI_MISO", sx, sy, "SPI_MISO", is_global=True, shape="output")
            w.label_at_pin(NCE, "SPI_SCK", sx, sy, "SPI_SCK", is_global=True, shape="input")
            w.label_at_pin(NCE, "SPI_CS", sx, sy, "SPI_CS", is_global=True, shape="input")
        else:
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    w.label_at_pin(TFLN, "VDD_1V8", tfln_x, tfln_y, "+1V8", is_global=True, shape="input")
    w.label_at_pin(TFLN, "VDD_3V3", tfln_x, tfln_y, "+3V3", is_global=True, shape="input")
    w.label_at_pin(TFLN, "GND", tfln_x, tfln_y, "GND", is_global=True, shape="passive")
    w.label_at_pin(TFLN, "SDA", tfln_x, tfln_y, "I2C_SDA", is_global=True)
    w.label_at_pin(TFLN, "SCL", tfln_x, tfln_y, "I2C_SCL", is_global=True, shape="input")

    # RF Drivers
    for i in range(4):
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            w.label_at_pin(ISL_VRM, f"PWM{ph}", sx, sy, f"VRM{i}_PWM{ph}")
        w.label_at_pin(ISL_VRM, "VCC", sx, sy, "+12V", is_global=True, shape="input")
        w.label_at_pin(ISL_VRM, "GND", sx, sy, "GND", is_global=True, shape="passive")
        w.label_at_pin(ISL_VRM, "SDA", sx, sy, "I2C_SDA", is_global=True)
        w.label_at_pin(ISL_VRM, "SCL", sx, sy, "I2C_SCL", is_global=True, shape="input")
        w.label_at_pin(ISL_VRM, "VSEN_P", sx, sy, "+0V8", is_global=True, shape="input")
        w.no_connect(ISL_VRM, "PGOOD", sx, sy)
        w.label_at_pin(ISL_VRM, "EN", sx, sy, "+3V3", is_global=True, shape="input")
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        sx = 200 + i * 250
        sy = 1400
        w.place(SI, f"U{250 + i}", "Si5395A", sx, sy)
        w.label_at_pin(SI, "SDA", sx, sy, "I2C_SDA", is_global=True)
        w.label_at_pin(SI, "SCL", sx, sy, "I2C_SCL", is_global=True, shape="input")
        for out in range(4):
            w.label_at_pin(SI, f"OUT{out}P", sx, sy, f"CLK{i}_OUT{out}P")
            w.label_at_pin(SI, f"OUT{out}N", sx, sy, f"CLK{i}_OUT{out}N")
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            w.no_connect(PEX, f"DN{dn}_BUS", sx, sy)
        w.label_at_pin(PEX, "REFCLK_P", sx, sy, f"CLK{i // 2}_OUT{(i % 2) + 2}P")
        w.label_at_pin(PEX, "REFCLK_N", sx, sy, f"CLK{i // 2}_OUT{(i % 2) + 2}N")
        w.label_at_pin(PEX, "SMBUS_DATA", sx, sy, "I2C_SDA", is_global=True)
        w.label_at_pin(PEX, "SMBUS_CLK", sx, sy, "I2C_SCL", is_global=True, shape="input")
        w.label_at_pin(PEX, "VDD_0V9", sx, sy, "+0V9", is_global=True, shape="input")
        w.label_at_pin(PEX, "VDD_1V8", sx, sy, "+1V8", is_global=True, shape="input")
        w.label_at_pin(PEX, "GND", sx, sy, "GND", is_global=True, shape="passive")
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
    bmc_x, bmc_y = 200, 2170
    w.place(AST, "U380", "AST2600", bmc_x, bmc_y)
    w.label_at_pin(AST, "I2C0_SDA", bmc_x, bmc_y, "I2C_SDA", is_global=True)
    w.label_at_pin(AST, "I2C0_SCL", bmc_x, bmc_y, "I2C_SCL", is_global=True, shape="input")
    w.label_at_pin(AST, "I2C1_SDA", bmc_x, bmc_y, "I2C_SDA", is_global=True)
    w.label_at_pin(AST, "I2C1_SCL", bmc_x, bmc_y, "I2C_SCL", is_global=True, shape="input")
    w.label_at_pin(AST, "SPI0_MOSI", bmc_x, bmc_y, "SPI_MOSI", is_global=True, shape="output")
    w.label_at_pin(AST, "SPI0_MISO", bmc_x, bmc_y, "SPI_MISO", is_global=True, shape="input")
    w.label_at_pin(AST, "SPI0_SCK", bmc_x, bmc_y, "SPI_SCK", is_global=True, shape="output")
    w.label_at_pin(AST, "SPI0_CS0", bmc_x, bmc_y, "SPI_CS", is_global=True, shape="output")
    w.label_at_pin(AST, "VDD_1V8", bmc_x, bmc_y, "+1V8", is_global=True, shape="input")
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
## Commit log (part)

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2026-02-20 Upgrade to LightRail AI: 20-Layer Photonic Intelligence Stack
2026-04-10 Add LightRail LPO 1.6T Photonic Accelerator PCB design
    Complete KiCad design files for the LightRail LPO 1.6T Gen3 Photonic
    Accelerator board:
    Schematic (.kicad_sch):
    - 8 custom IC symbols: TFLN modulator (U1), DFB laser array (U2),
    Si5395A clock gen (U3), AD5684R quad DAC (U4), MAX3669 laser
    driver (U5), TPS7A2018 LDO (U6), TPS54360 buck (U7), MPT5000
2026-04-10 Regenerate PCB file with updated generator script
2026-04-11 fix: correct net IDs on power zones, DDR5 traces, and via_diameter DRC violation
    - V_CORE_U0 zones (In3.Cu, In4.Cu): net 0 → net 164
    - V_CORE_U1 zones (In5.Cu, In6.Cu): net 0 → net 165
    - GND zone (In7.Cu): net 0 → net 1 (matching existing GND zones)
    - DDR5 fly-by CK segments: net 0 → net 152/153 (U0) and 160/161 (U1)
    - DDR5_Data net class via_diameter: 0.25mm → 0.3mm (meets min_via_diameter)
2026-04-17 fix(pcb,docs): address Devin Review findings
    - Stackup: V_CORE_U1 planes (In5.Cu, In6.Cu) go from 0.5 oz to 2 oz so
    U1 matches U0 PDN impedance (previous 4:1 asymmetry would have
    violated the 10 mV IR-drop target for V_CORE_U1)
    - .kicad_pcb stackup: bump In5.Cu / In6.Cu thickness 0.0175 -> 0.035 mm
    - gerber_layers.txt In5/In6 re-labelled as V_CORE_U1 planes (the zones
    there already carry net 165 = V_CORE_U1; docs now match PCB)
2026-04-17 fix(pcb,sch,drc): make files kicad-cli-parseable + VDDQ + DRC regex
    Net result: 'kicad-cli pcb export gerbers' now successfully produces a
    full fab package (gerbers/, drill/, assembly/, docs/) from the scaffold.
    PCB edits (needed for kicad-cli to parse):
    - Strip top-level ';; comment' lines from .kicad_pcb (KiCad S-expr
    parser rejects them outside of whitespace positions)
    - Remove '(id N)' tokens from footprint 'property' blocks (that form
2026-04-17 fix(bom,sch): TFLN 0.9V LDO -> ADP7118-0.9; root sch date 04-11
    Two Devin Review findings:
    1. fab/generate_bom.py assigned MPN ADM7150ARDZ-5.0 to U36 with a
    description of 'TFLN 0.9 V RF supply (configured 0.9V)'. ADM7150
    is a fixed-output LDO and the -5.0 suffix means it outputs 5.0 V,
    not 0.9 V; procuring from this BOM would blow the TFLN driver.
    Switch to ADP7118ACPZ-0.9-R7 (Analog Devices fixed 0.9 V ultra-
2026-04-17 fix(pcb): DDR5 CK diff pair gap 2.0->0.25 mm; general thickness 1.6->1.86
    Two Devin Review findings on the PCB file:
    1. DDR5 CK differential pairs (nets 152/153 U0, 160/161 U1) were laid
    out on In2.Cu with CK_P at y=72 and CK_N at y=74 -- a 2.0 mm
    center-to-center gap on a net class whose diff_pair_gap is 0.15 mm.
    That's ~13x the design rule and gives basically no differential
    coupling. Move all 8 CK_N stub segments to y=72.25 so the pair is
2026-04-17 fix(pcb,docs): remove conflicting plane zones; fix impedance refs; thickness 1.86->1.81
    Three Devin Review findings on the stackup-symmetry follow-up:
    1. Conflicting zones on V_CORE layers. The previous scaffold put
    board-wide +12V on In3.Cu, +3V3 on In4.Cu, and GND on In5.Cu.
    After the recent re-tasking of In3..In6 as dedicated V_CORE_U0 /
    V_CORE_U1 planes (with explicit V_CORE_U0 zones on In3+In4 and
    V_CORE_U1 zones on In5+In6), those old full-board zones would
2026-04-17 feat: HBM4 co-packaged memory migration (DDR5 -> HBM4 interposer)
    Replace discrete DDR5-8800 DIMM fly-by subsystem with a co-packaged
    NCE+HBM4-on-interposer topology per vendor reference (SK hynix /
    Micron 12-Hi, 48 GB/stack, 8 Gbps/pin, 1024-bit bus).
    PCB (LightRail_LPO_1.6T.kicad_pcb):
    - Remove 8x DDR5 DIMM footprints (U202/U204/U206/U208 + U2102/..)
    - Add 8x HBM4_Stack_11x11mm footprints (U103-U106 flanking U101,
2026-04-17 fix(footprint): DrMOS pad names PVCC/PWM/DRVH/.../BOOT -> numeric 1..8
    KiCad netlist generation maps schematic pin *numbers* to footprint pad
    *names* as identical strings. The ISL99390_DrMOS symbol in
    VRM.kicad_sch:25-32 uses numeric pin numbers 1..8 (PVCC=1, PWM=2,
    DRVH=3, DRVL=4, PHASE=5, IMON=6, PGND=7, BOOT=8), but the footprint
    was using the functional names verbatim, so all 48 DrMOS instances
    (U302-U349 across both 24-phase VRMs) would have failed pad-to-net
2026-04-19 fix(rev6): address Devin Review findings
    - PWR_CORE net class clearance 0.3 -> 0.4 mm in .kicad_pro to match
    README.md §4 and fab/drc_custom.kicad_dru rule pdn_high_current_clearance;
    interactive router will now preview the same 0.4 mm clearance that the
    custom DRC enforces.
    - Add TFLN_ELEC_TRANSITION to the backdrill_required_high_speed DRC rule
    condition so through-vias on the TFLN electrical-transition stubs are
2026-04-19 fix(rev6): address Devin Review findings (round 4)
    - HBM4 REFCK skew reconciled across DRC + docs. Physical target is
    ~2 ps (0.3 mm on Megtron-7 stripline, eps_r = 3.3) as stated in
    docs/Architecture.md §2 and Tapeout_Checklist.md §3. Updated
    docs/DFM_Checklist.md §7.2 (±0.025 mm -> ±0.3 mm, 2 ps) and
    docs/SI_PI_Thermal_Plan.md §1.3 to match. PCIe / TFLN intra-pair
    skew stays at ±0.025 mm (§7.3 unchanged). Fixed misleading
2026-05-06 chore(sch): bump rev 4.0 -> 6.1 and date in schematic title blocks
2026-05-06 feat(rev6.2): add +3V3/+1V8 inner power planes (In7/In8) + fab readiness signoff
    - inject inner-layer power planes for +3V3 (In7.Cu) and +1V8 (In8.Cu)
    with full-board coverage, 0.25mm thermal gap, 0.3mm thermal bridge
    - add docs/Fab_Readiness_Signoff.md covering manufacturing release scope,
    IPC-6012 Class 3 compliance, deferred items for Rev 6.3 interactive
    routing, and release recommendation (engineering panels OK, hold for
    production tape-out)
2026-05-07 feat(LR-S1A): architectural BOM for 1U 51.2 Tbps CPO switch
    New product line — separate from LR-P3A compute node — covering the 1U
    co-packaged-optics network switch shown in the LightRail AI reference image.
    - docs/LR-S1A_CPO_Switch_BOM.md: 7-section architectural BOM with all
    five user-defined functional categories (CPO assembly, optical routing,
    front-panel interfaces, secondary circuitry & power delivery, chassis),
    vendor short-list, lead-time table, and standards/compliance matrix.
2026-05-11 feat(LR-S1A): Rev 1.0 manufacturing release — 440x550 mm 1U CPO switch motherboard
    - 18-layer HDI stackup (Megtron-7 / High-Tg FR-4 / Faradflex BC24)
    - KiCad 8 native (schema 20240108), 197 footprints, 14 zones, 149 vias, 1332 nets
    - Placement parity with reference image: ASIC + 16 CPO engines composite,
    24-phase V_ASIC + 8-phase V_OPT DrMOS rings, 96-cap decoupling ring,
    8 ELSFP cages, 32 OSFP-XD cages (2 stacked rows per side), mgmt cluster,
    2x CRPS-1U PSU bays, 7 fan headers, Samtec ARC daughterboard, 8 MH + 4 FID
2026-05-18 fix: correct PDN decoupling cap net IDs (312-449, not 15-152)
    The generate_decoupling_caps() function was using start_net_id=15 for
    U0 and 84 for U1, but PDN_U0_T4_C0..PDN_U1_T1_C5 nets are actually
    defined at IDs 312-449 in generate_nets(). This caused 138 'Net name
    doesn't match ID' parse errors when KiCad loaded the PCB.
    DRC now reports 0 net ID mismatches. Remaining 1608 violations are
    expected baseline issues (silk overlap, solder mask bridges, clearances
2026-05-18 feat: schematic-ECO net assignment, B.Cu routing, VRM ICs, denser passives, fab package
    - Schematic-ECO: assign real nets to swept arc traces, passive fill components
    - B.Cu perimeter routing: 24 horizontal bottom, 16 vertical left/right edges
    - VRM controller ICs: 6x ISL69260 QFN-48 at board corners/edges
    - Dense passive fill: 6-row 0402 bands, side bands, 0805 arrays, ferrite beads
    - 0201 bypass caps on 8mm grid, B.Cu passives under NCEs
    - Fab package: 228MB (42 Gerbers, ODB++, drill, BOM, PnP, STEP)
2026-05-18 feat: add GSD netlist, KiCad native netlist, and full KiCad project files to fab release
2026-05-19 feat: regenerate PCB with QPA components (23,259 segments, 2,794 footprints)
2026-05-19 feat: add IPC-2581C unified manufacturing package
2026-05-21 feat: add QPA/NCE system block diagram (PNG + generator script)
2026-05-21 feat: add PDF output for block diagram
2026-05-25 feat: Dual-ASIC Accelerator Board RTL, verification, and synthesis ecosystem
    Complete hardware design ecosystem for the symmetrical Dual-NCE accelerator:
    RTL Modules (SystemVerilog, synthesizable):
    - nce_top.sv: Top-level chip wrapper with Node A/B strap configuration
    - chip_to_chip_bridge.sv: 64-bit DDR source-synchronous bridge (64 Gbps)
    with CRC-32 integrity, credit-based flow control, auto-retry buffer
    - bridge_tx.sv / bridge_rx.sv: Packetized TX/RX datapaths
2026-05-26 feat: NCE/TFLN chip design validation — RTL, specs, block diagrams, MPW shuttle plan
    Design validation deliverables for SMIC 28nm/40nm MPW shuttle:
    RTL (2 new Verilog designs):
    - rtl/nce_core/nce_compute_core.v: NCE compute core with 128-way SIMD
    (8-lane MPW subset), AXI4-Lite CXL interface, DMA, thermal management,
    DVFS, power gating, and QPA trigger output
    - rtl/tfln_optical_engine/tfln_optical_engine.v: TFLN optical engine
2026-06-05 feat: add kicad-happy EDA skills for fab-ready PCB designs
    Integrated full kicad-happy skill suite (from github.com/aklofas/kicad-happy):
    - kicad: Schematic/PCB analysis, DRC/ERC, power tree, subcircuit detection
    - spice: SPICE simulation (ngspice/LTspice/Xyce), filter/divider validation
    - emc: EMC pre-compliance (42 rules, FCC/CISPR/automotive/MIL-STD-461G)
    - bom: BOM lifecycle management, multi-distributor sourcing
    - digikey: DigiKey component search + datasheet download
2026-06-05 Add eval board testing skill for 22-layer validation
2026-06-06 refactor: improve ERC quality via grid snapping and power flags
2026-06-17 feat: TinyTapeout Sky130 submission — GDSII + Verilog for LightRail NCE MAC unit
    - 8-bit MAC engine (tt_um_lightrail_nce) — core compute cell of the NCE
    - 8x8 multiply, 16-bit accumulator, ReLU activation, quantization shift
    - OpenLane hardening complete: 0 DRC violations, LVS clean, 0 timing violations
    - 662 standard cells, 50 MHz on Sky130 (sky130_fd_sc_hd)
    - 5 cocotb tests (MAC, accumulate, ReLU negative, shift quantization, status)
    Deliverables: tinytapeout/src/project.v — RTL source
2026-06-18 Add lightrail-asic-integration/constraints/lightrail_bga2500_io.tcl
2026-06-18 Add lightrail-asic-integration/scripts/run_flow.sh
2026-06-20 feat: eval board DRC clean (0 shorts, 0 crossings) + production Gerbers
    Eval Board (fab/eval_board/):
    - 88 footprints placed (dual NCE: U1 + U4)
    - 22-layer stackup with 11 copper zones (8 GND + 3 power planes)
    - 136 vias (92 power + 12 GND stitching)
    - DRC: 0 shorting_items, 0 tracks_crossing
    - 33 Gerber X2 files + Excellon drill generated
